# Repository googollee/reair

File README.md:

# ReAir

ReAir 是一套面向公寓的分布式通风系统，主要目的是降低室内二氧化碳。集中式通风需要风管和有线控制器，后装困难；ReAir 改用多个可反转的风扇节点，节点之间无需有线连接，仅通过本地 Wi-Fi 协同，不依赖互联网。

- 每个节点都是独立的 Matter 设备，带外壳，可装在风道上，外壳上有配对二维码；可被 Home Assistant 等控制器单独控制。
- 节点有「主」「从」「独立」三种角色，可通过 Matter 切换，立即生效：
  - 主：设定风向模式、往复周期和风力，并向从节点同步风向和风力。
  - 从：跟随主节点的风向和风力，不能在从节点上直接修改；主节点离线时保持最后状态继续运行，重启后保持静止，直到收到主节点同步。
  - 独立：不同步也不跟随，单独设定风向与风力。
- 风向模式有固定正向、固定反向和往复切换，往复按设定周期正反切换，以节约能源；风力至少有高、中、低三档，关闭视为风力的特殊取值。
- 每个节点可选择「正向」对应进气还是排气（默认排气），并可只读查看当前实际风向（进气、排气或停止）。
- 系统只保证一个主节点：局域网内出现多个主节点时，节点记录警告状态，用户可通过 Matter 查看并清除。

不含传感器和自动控制策略，用户在 Matter 控制器中根据二氧化碳读数等自行编写规则；也不考虑局域网内的安全防护。详见 [docs/prd.md](docs/prd.md)。

## 目录

- `firmware/`：节点固件（ESP-IDF + esp-matter）
- `hardware/`：PCB 与外壳
- `config/`：配对信息、证书等配置
- `scripts/`：构建辅助脚本
- `docs/`：文档（PRD、设计、ADR），规则见 [docs/README.md](docs/README.md)
- `out/`：构建产物（由 make 生成）

## 构建

固件依赖 ESP-IDF 和 esp-matter，默认在 `~/esp` 下，可用 `IDF_DIR`、`ESP_MATTER` 覆盖。运行 `make help` 查看所有命令。

| 命令 | 说明 |
| --- | --- |
| `make env` | 准备固件编译环境（浅克隆 ESP-IDF 和 esp-matter，安装工具链，已装的跳过） |
| `make attestation` | 从 SDK 提取测试证书到 `config/attestation/test/` |
| `make config` | 根据 `config/` 生成 factory 分区镜像和 sdkconfig 片段 |
| `make build` | 编译固件（默认目标） |
| `make flash PORT=...` | 烧录固件和 factory 分区 |
| `make flash-factory PORT=...` | 只烧录 factory 分区 |
| `make pcb` | 导出 PCB 生产文件（Gerber、BOM、贴片坐标）到 `out/pcb/` |
| `make enclosure` | 渲染外壳各零件（3MF）到 `out/enclosure/`，需要 OpenSCAD |
| `make test` | 主机上的单元测试 |
| `make test-ota-rollback PORT=...` | OTA 回退的板上测试 |
| `make test-e2e` | 两块板的端到端同步测试 |
| `make clean` | 清除 `out/` |

常用变量：`PORT=/dev/cu.usbmodemXXXX`（烧录和板上测试）、`TARGET=esp32c3|esp32s3`（默认 `esp32c3`）。

典型流程：

```sh
make env
make build
make flash PORT=/dev/cu.usbmodemXXXX
```

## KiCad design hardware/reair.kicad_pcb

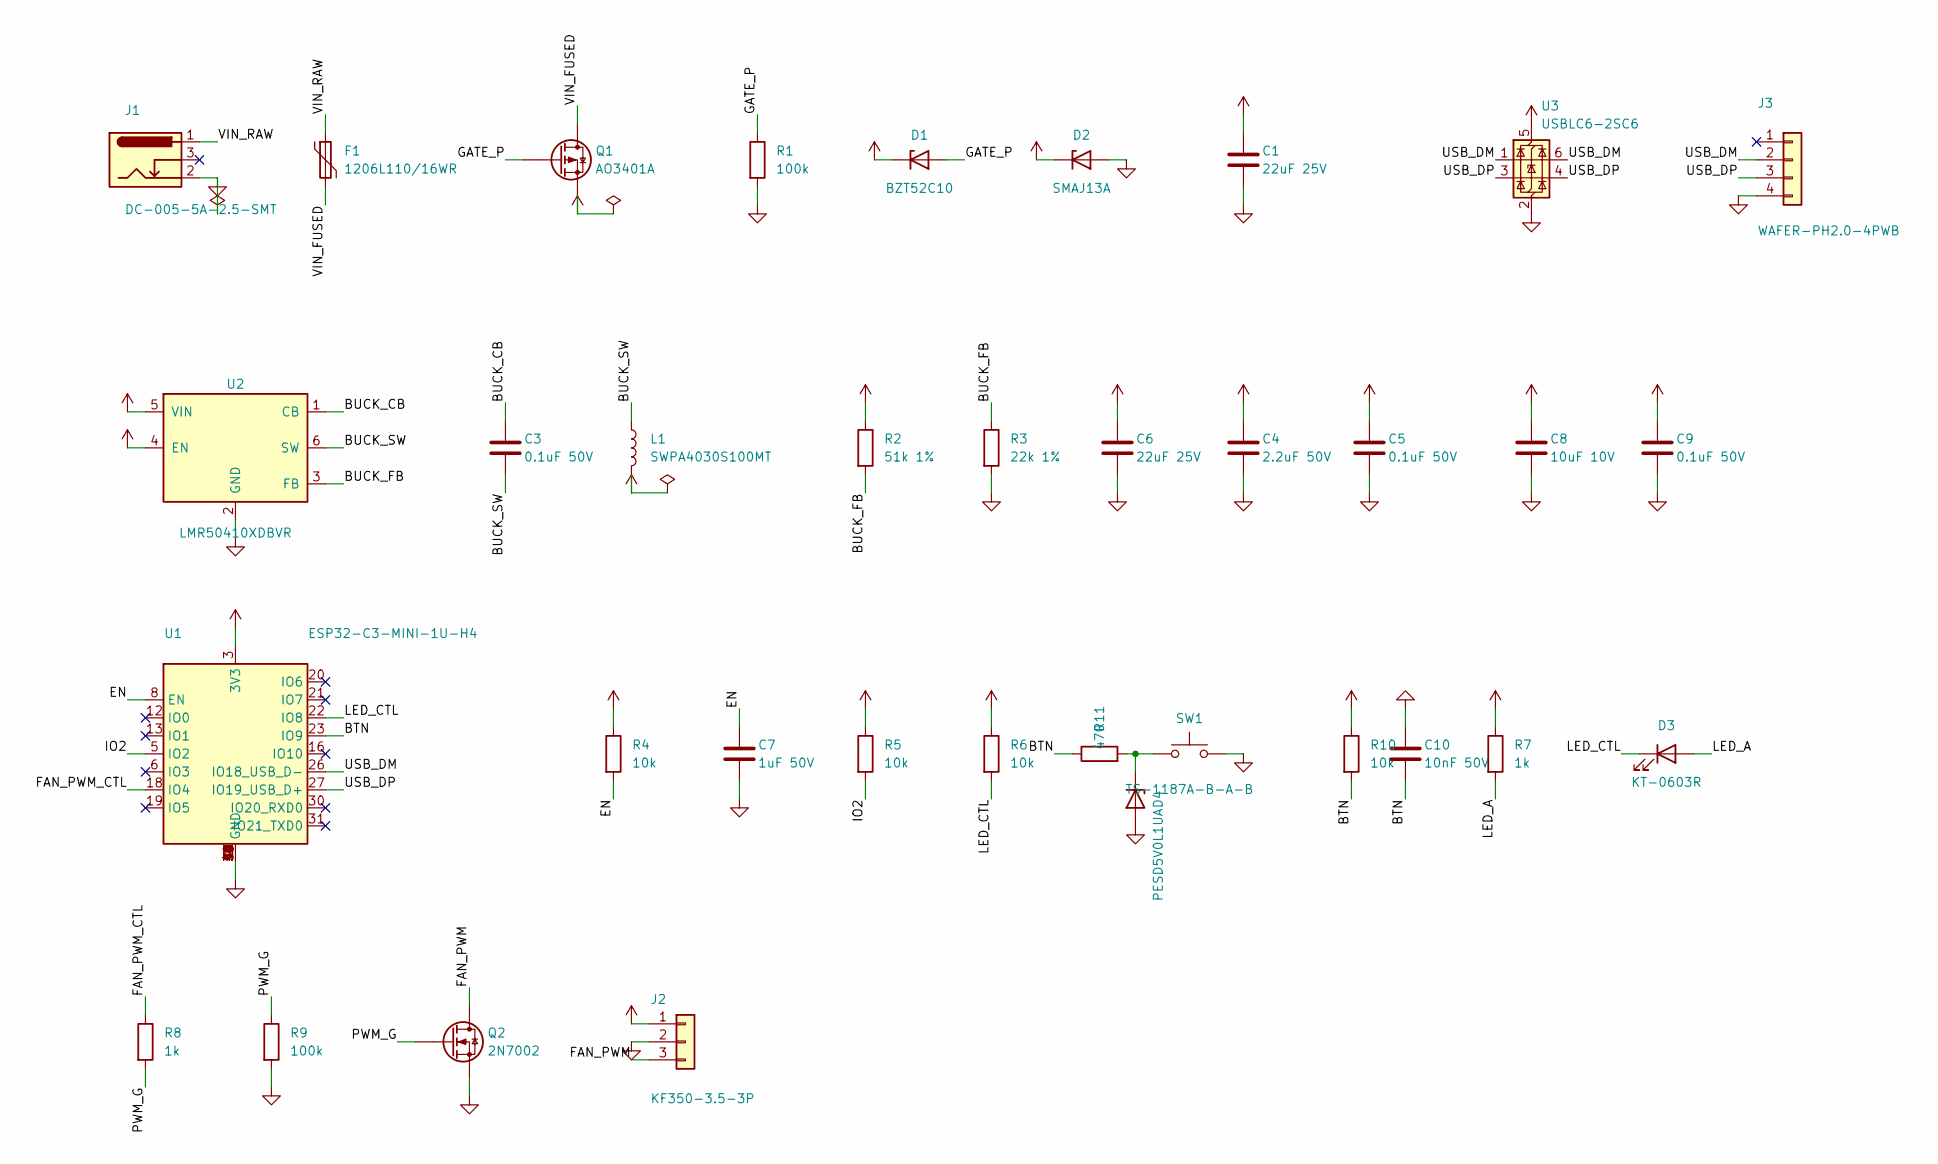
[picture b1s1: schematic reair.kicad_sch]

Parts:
C1, C6: 22uF 25V; C_0805_2012Metric; LCSC C45783
C3, C5, C9: 0.1uF 50V; C_0603_1608Metric; LCSC C14663
C4: 2.2uF 50V; C_0805_2012Metric; LCSC C377773
C7: 1uF 50V; C_0603_1608Metric; LCSC C15849
C8: 10uF 10V; C_0603_1608Metric; LCSC C19702
C10: 10nF 50V; C_0603_1608Metric; LCSC C57112
D1: BZT52C10; D_SOD-123; LCSC C2103
D2: SMAJ13A; D_SMA; LCSC C148214
D3: KT-0603R; LED_0603_1608Metric; LCSC C2286
D4: PESD5V0L1UA; D_SOD-323; LCSC C552555
F1: 1206L110/16WR; Fuse_1206_3216Metric; LCSC C3761685
J1: DC-005-5A-2.5-SMT; BarrelJack_XKB_DC-005-5A-2.5-SMT; LCSC C319133
J2: KF350-3.5-3P; TerminalBlock_KF350-3.5-3P; LCSC C474893
J3: WAFER-PH2.0-4PWB; JST_PH_S4B-PH-SM4-TB_1x04-1MP_P2.00mm_Horizontal; LCSC C3029442
L1: SWPA4030S100MT; L_Sunlord_SWPA4030S; LCSC C38117
Q1: AO3401A; SOT-23; LCSC C15127
Q2: 2N7002; SOT-23; LCSC C8545
R1, R9: 100k; R_0603_1608Metric; LCSC C25803
R2: 51k 1%; R_0603_1608Metric; LCSC C23196
R3: 22k 1%; R_0603_1608Metric; LCSC C31850
R4, R5, R6, R10: 10k; R_0603_1608Metric; LCSC C25804
R7, R8: 1k; R_0603_1608Metric; LCSC C21190
R11: 470; R_0603_1608Metric; LCSC C23179
SW1: TS-1187A-B-A-B; SW_Push_1P1T_XKB_TS-1187A; LCSC C318884
U1: ESP32-C3-MINI-1U-H4; ESP32-C3-MINI-1U; LCSC C3013922
U2: LMR50410XDBVR; SOT-23-6; LCSC C2841056
U3: USBLC6-2SC6; SOT-23-6; LCSC C7519

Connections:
+3V3: C6.1, C8.1, C9.1, L1.2, R2.1, R4.1, R5.1, R6.1, R7.1, R10.1, U1.3 (3V3), U3.5 (VBUS)
+12V: C1.1, C4.1, C5.1, D1.1 (K), D2.1 (K), J2.1, Q1.2 (S), U2.4 (EN), U2.5 (VIN)
/BTN: C10.2, R10.2, R11.1, U1.23 (IO9)
/BUCK_CB: C3.1, U2.1 (CB)
/BUCK_FB: R2.2, R3.1, U2.3 (FB)
/BUCK_SW: C3.2, L1.1, U2.6 (SW)
/EN: C7.1, R4.2, U1.8 (EN)
/FAN_PWM: J2.3, Q2.3 (D)
/FAN_PWM_CTL: R8.1, U1.18 (IO4)
/GATE_P: D1.2 (A), Q1.1 (G), R1.1
/IO2: R5.2, U1.5 (IO2)
/LED_A: D3.2 (A), R7.2
/LED_CTL: D3.1 (K), R6.2, U1.22 (IO8)
/PWM_G: Q2.1 (G), R8.2, R9.1
/USB_DM: J3.2, U1.26 (IO18_USB_D-), U3.1 (I/O1), U3.6 (I/O1)
/USB_DP: J3.3, U1.27 (IO19_USB_D+), U3.3 (I/O2), U3.4 (I/O2)
/VIN_FUSED: F1.2, Q1.3 (D)
/VIN_RAW: F1.1, J1.1
GND: C1.2, C4.2, C5.2, C6.2, C7.2, C8.2, C9.2, C10.1, D2.2 (A), D4.2 (A), J1.2, J2.2, J3.4, Q2.2 (S), R1.2, R3.2, R9.2, SW1.2, U1.1 (GND), U1.2 (GND), U1.11 (GND), U1.14 (GND), U1.36 (GND), U1.37 (GND), U1.38 (GND), U1.39 (GND), U1.40 (GND), U1.41 (GND), U1.42 (GND), U1.43 (GND), U1.44 (GND), U1.45 (GND), U1.46 (GND), U1.47 (GND), U1.48 (GND), U1.49 (GND), U1.50 (GND), U1.51 (GND), U1.52 (GND), U1.53 (GND), U2.2 (GND), U3.2 (GND)
unnamed: D4.1 (K), R11.2, SW1.1

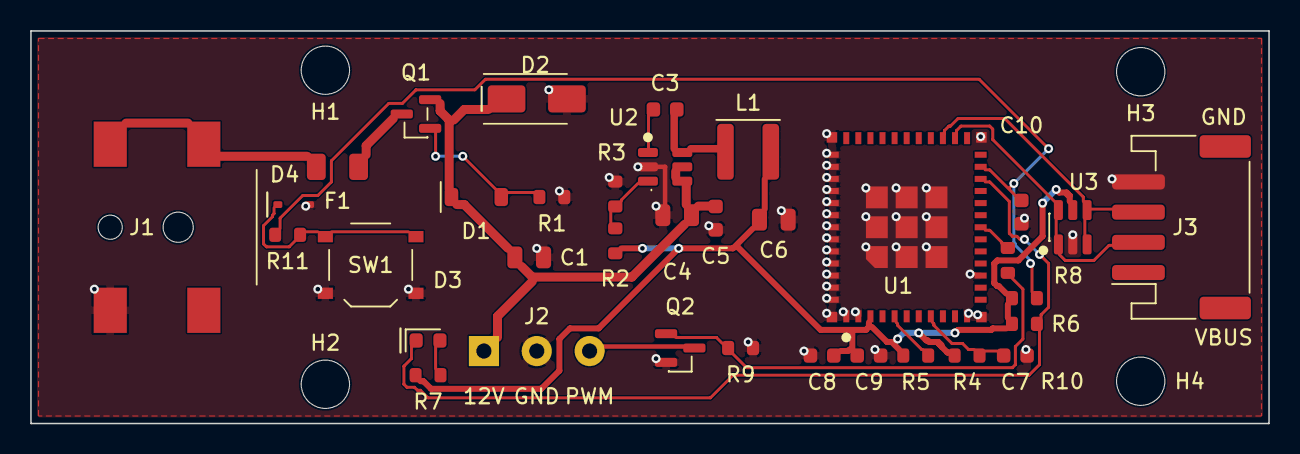
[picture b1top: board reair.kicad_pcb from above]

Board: 2 copper layers, 82.0 x 26.0 mm, 39 parts (0 on the bottom side), 20 nets.

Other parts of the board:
H1, H2, H3, H4: MountingHole_3.2mm_M3
